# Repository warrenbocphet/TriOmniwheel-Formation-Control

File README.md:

# 3-OmniWheels-Rover-Platform
This project developed by students in [the University of Adelaide](https://ecms.adelaide.edu.au/electrical-electronic-engineering/) during the Summer Research project 2018-2019, which developed a 3WD  rover platform for autonomous multi-agent systems.

## Overview:
>The distributed system will contain multiple agents. Each agent can make its own decision. However, the four agents still need to communicate with each other about the velocity, the current position, the destination and the angle of the agent. This allows an agreement to be made to achieve the desired formation.

## Hardware setup:
Motor: 251RPM DC geared (43.7:1) motor w/ ecoder.

Encoder: 64 resolution => 2797 count per rotation.

Control board: Arduino Due for controlling, Arduino MKR1000 for WiFi communication.

## Example
### Simple case (user generated coordinate/path)
Real data feedback and put into simulation

Real demo. Noticed how the position of the rovers and the feedback position is not entirely the same. Overtime, the system introduce more and more error. Since the system is self guidance, there's no correction during performance.

### Formation control without collision avoidance
Generate path to form a triangle formation. Connected circle represent rover with radius, dash circle represent the safety distance (collision avoicedance is not implement in the GIF below).

The same triangle formation with different starting position. Noticed how the formation is rotated with these starting positions. The algorithm [1] does not try to get to a specific coordinate but rather a formation (i.e, a triangle, circle or any arbitrary topology).

### Formation control with collision avoidance
The collision avoidance will be explained further down, let's first have a look at the simulation and the result:

#### Hexagon

#### Triangle

#### X shape

#### Cross

#### Accumulating error (youtube link)

#### Reducing accumulating error by reducing the speed (youtube link)

## Reference
[1] Fathian, Kaveh & Safaoui, Sleiman & Summers, Tyler & Gans, Nicholas. (2018). Robust Distributed Planar Formation Control for Higher-Order Holonomic and Nonholonomic Agents. Link: https://www.researchgate.net/publication/326696917_Robust_Distributed_Planar_Formation_Control_for_Higher-Order_Holonomic_and_Nonholonomic_Agents

The author's website: https://sites.google.com/view/kavehfathian/home?authuser=0

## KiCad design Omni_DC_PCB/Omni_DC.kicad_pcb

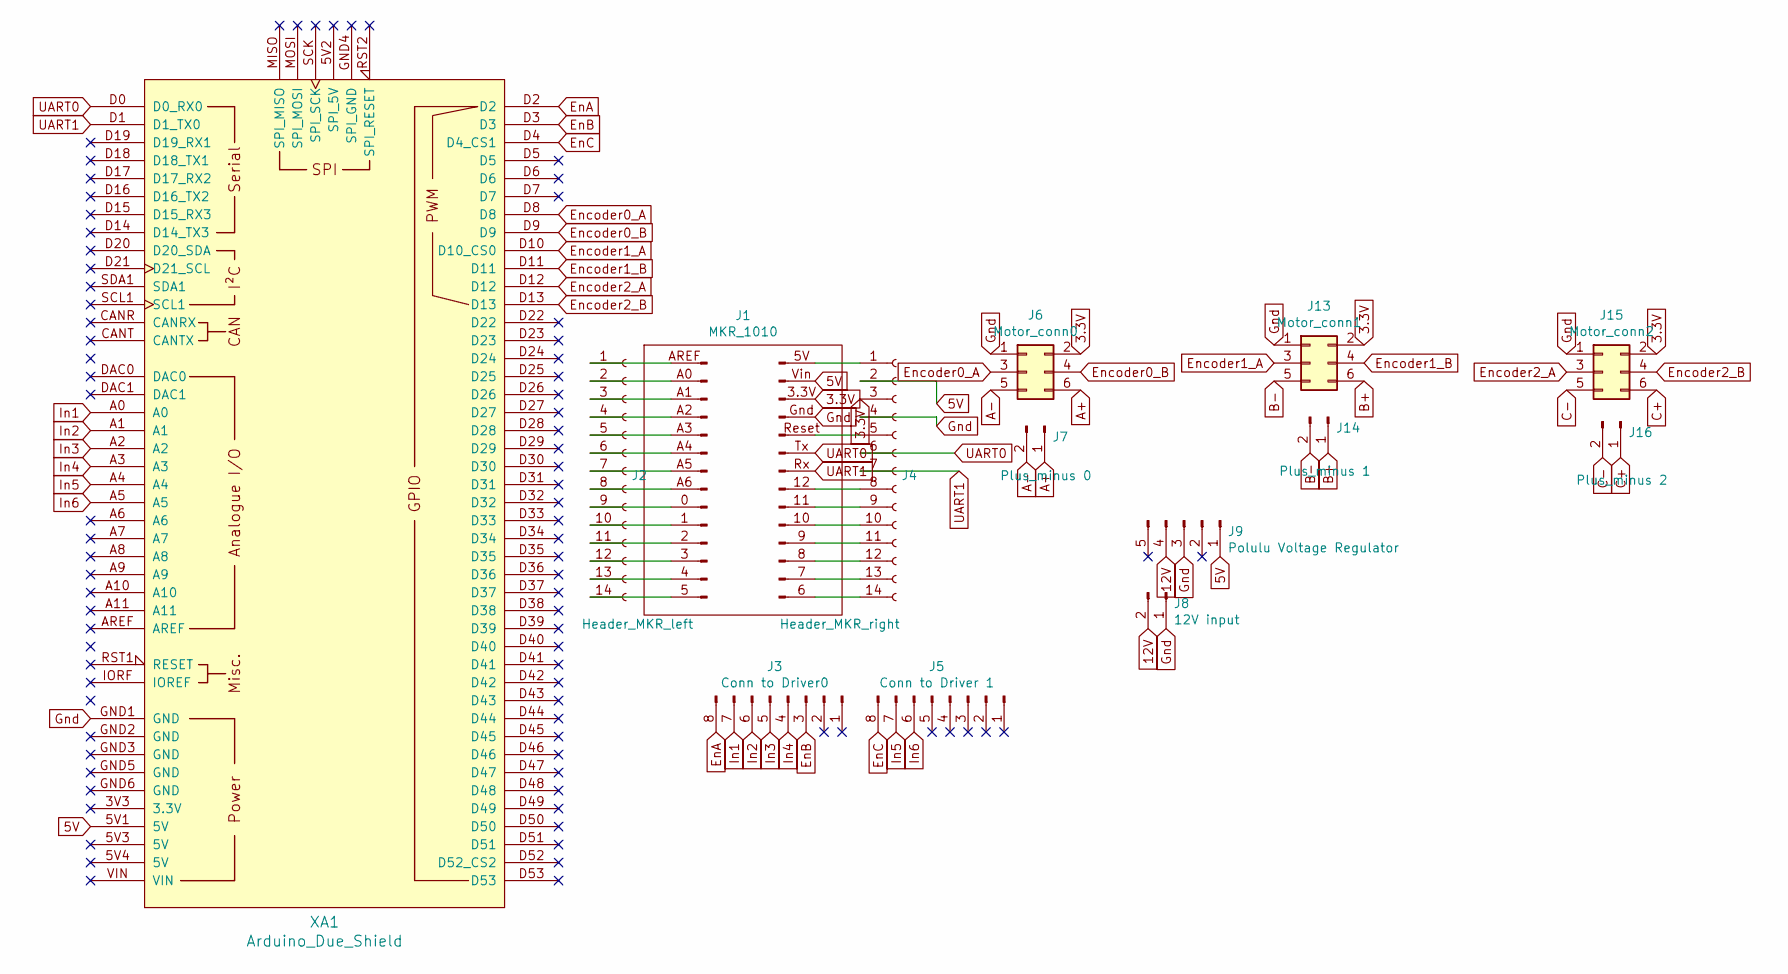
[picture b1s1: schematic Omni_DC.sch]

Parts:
J1: MKR_1010
J2: Header_MKR_left; PinHeader_1x14_P2.54mm_Vertical
J3: Conn to Driver0; PinHeader_1x08_P2.54mm_Vertical
J4: Header_MKR_right; PinHeader_1x14_P2.54mm_Vertical
J5: Conn to Driver 1; PinHeader_1x08_P2.54mm_Vertical
J6: Motor_conn0; PinHeader_2x03_P2.54mm_Vertical
J7: Plus_minus 0; PinHeader_1x02_P2.54mm_Vertical
J8: 12V input; PinHeader_1x02_P2.54mm_Vertical
J9: Polulu Voltage Regulator; PinHeader_1x05_P2.54mm_Vertical
J13: Motor_conn1; PinHeader_2x03_P2.54mm_Vertical
J14: Plus_minus 1; PinHeader_1x02_P2.54mm_Vertical
J15: Motor_conn2; PinHeader_2x03_P2.54mm_Vertical
J16: Plus_minus 2; PinHeader_1x02_P2.54mm_Vertical
XA1: Arduino_Due_Shield

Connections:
3.3V: J1.3.3V (Pin_3), J4.3, J6.2, J13.2, J15.2
5V: J1.Vin (Pin_2), J4.2, J9.1, XA1.5V1 (5V)
12V: J8.2, J9.4
A+: J6.6, J7.1
A-: J6.5, J7.2
B+: J13.6, J14.1
B-: J13.5, J14.2
C+: J15.6, J16.1
C-: J15.5, J16.2
EnA: J3.8, XA1.D2
EnB: J3.3, XA1.D3
EnC: J5.8, XA1.D4 (D4_CS1)
Encoder0_A: J6.3, XA1.D8
Encoder0_B: J6.4, XA1.D9
Encoder1_A: J13.3, XA1.D10 (D10_CS0)
Encoder1_B: J13.4, XA1.D11
Encoder2_A: J15.3, XA1.D12
Encoder2_B: J15.4, XA1.D13
Gnd: J1.Gnd (Pin_4), J4.4, J6.1, J8.1, J9.3, J13.1, J15.1, XA1.GND1 (GND)
In1: J3.7, XA1.A0
In2: J3.6, XA1.A1
In3: J3.5, XA1.A2
In4: J3.4, XA1.A3
In5: J5.7, XA1.A4
In6: J5.6, XA1.A5
unnamed: J1.0 (Pin_6), J2.9
unnamed: J1.1 (Pin_5), J2.10
unnamed: J1.2 (Pin_4), J2.11
unnamed: J1.3, J2.12
unnamed: J1.4 (Pin_2), J2.13
unnamed: J1.5 (Pin_1), J2.14
unnamed: J1.5V (1), J4.1
unnamed: J1.6 (Pin_14), J4.14
unnamed: J1.7 (Pin_13), J4.13
unnamed: J1.8 (Pin_12), J4.12
unnamed: J1.9 (Pin_11), J4.11
unnamed: J1.10, J4.10
unnamed: J1.11 (Pin_9), J4.9
unnamed: J1.12 (Pin_8), J4.8
unnamed: J1.A0 (Pin_13), J2.2
unnamed: J1.A1 (Pin_12), J2.3
unnamed: J1.A2 (Pin_11), J2.4
unnamed: J1.A3 (Pin_10), J2.5
unnamed: J1.A4 (Pin_9), J2.6
unnamed: J1.A5 (Pin_8), J2.7
unnamed: J1.A6 (Pin_7), J2.8
unnamed: J1.AREF (Pin_14), J2.1
unnamed: J1.Reset (Pin_5), J4.5
UART0: J1.Tx (Pin_6), J4.6, XA1.D0 (D0_RX0)
UART1: J1.Rx (Pin_7), J4.7, XA1.D1 (D1_TX0)

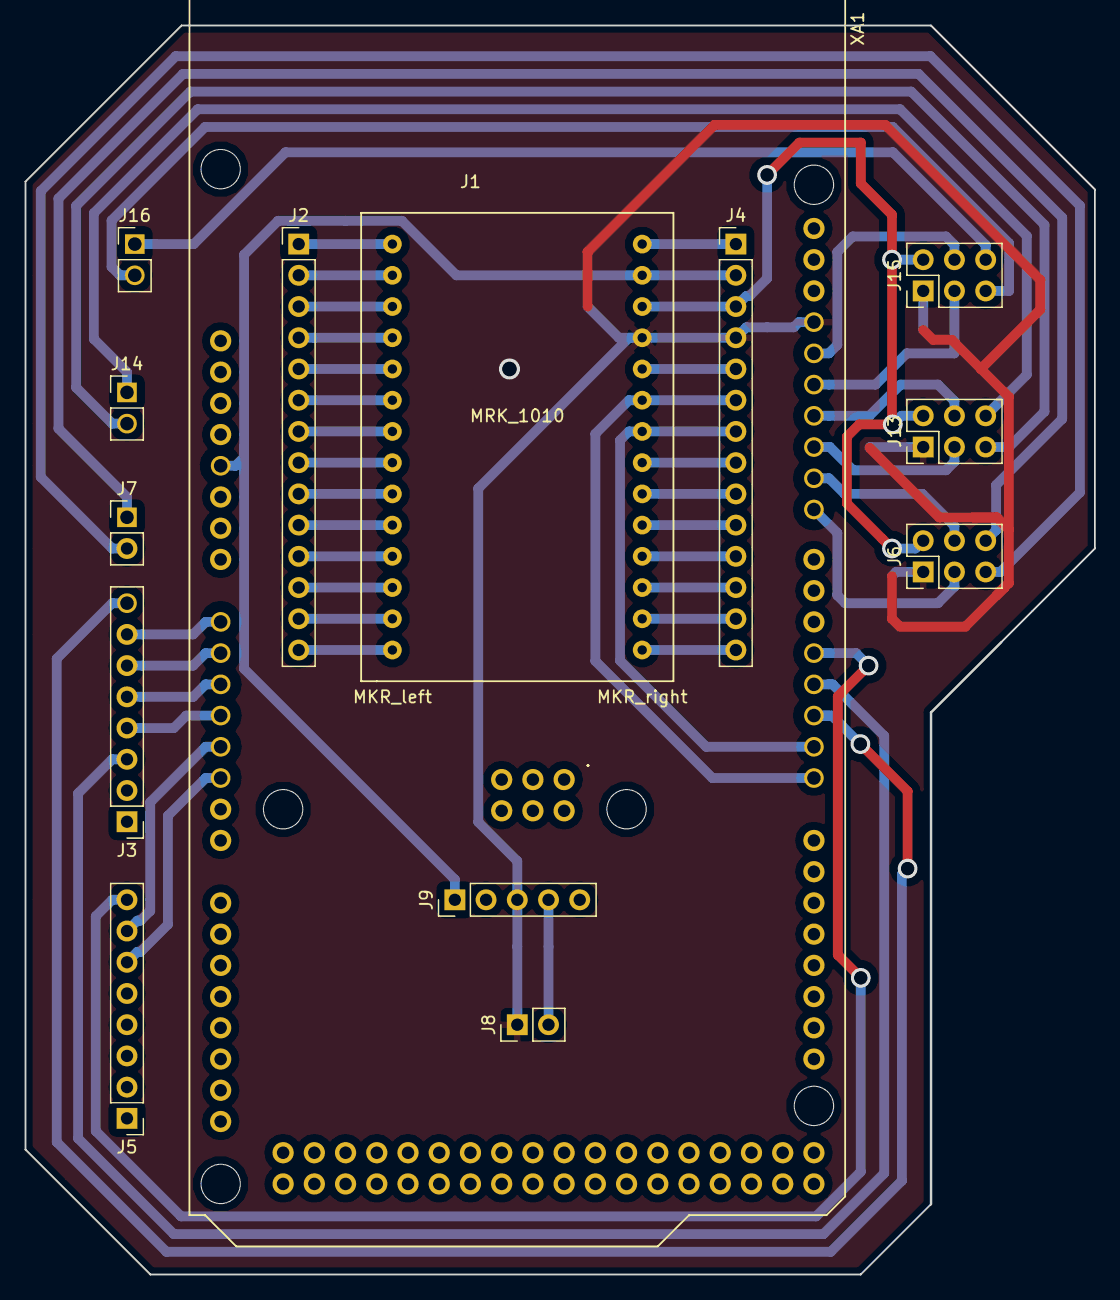
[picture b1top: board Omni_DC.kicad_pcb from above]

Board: 2 copper layers, 87.0 x 101.6 mm, 14 parts (0 on the bottom side), 50 nets.

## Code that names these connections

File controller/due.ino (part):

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///////////////////////////// DC motors /////////////////////////////
const int int1 = A0; // motor 0
const int int2 = A1;
const int enA = 2;
int pwm0;

const int int3 = A2; // motor 1
const int int4 = A3;
const int enB = 3;
int pwm1;

const int int5 = A4; // motor 2
const int int6 = A5;
const int enC = 4;
int pwm2;

float rover_radius = 13.7; // in cm
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
  pinMode(int1, OUTPUT);
  pinMode(int2, OUTPUT);
  pinMode(enA, OUTPUT);

  pinMode(int3, OUTPUT);
  pinMode(int4, OUTPUT);
  pinMode(enB, OUTPUT);

  pinMode(int5, OUTPUT);
  pinMode(int6, OUTPUT);
  pinMode(enC, OUTPUT);

  analogWrite(enA, 0);
  analogWrite(enB, 0);
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
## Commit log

2018-12-30 Add files via upload
    Arduino sketch that controls the speed of each wheel.
2018-12-30 Add files via upload
    The algorithm used to calculate the required speed of each wheel to reach the position and when to run those speed.
2018-12-30 Add files via upload
    API for the controller. Use to send and receive data through serial communication (UART) between Raspberry Pi and Arduino.
2018-12-30 Rename rapi0.py to rapi.py
2018-12-30 Update roverScheduler.py
    Fixed below bugs:
    - Cannot go to negative y
    - Cannot rotate on the spot
    - Cannot rotate to counterclockwise
2018-12-30 Update roverScheduler.py
    Create an upper limitation on how big the angular velocity can be.
2019-01-04 Update roverScheduler.py
    Fix a bug where rover can't run to negative x coordinate.
2019-01-07 Update roverScheduler.py
    Fix a bug where rover can't go to the same destination as the current destination.
2019-01-07 Update roverScheduler.py
    Fix a bug where rover would try to rotate even when the difference is ~0.
2019-01-07 Update roverScheduler.py
    fix a small bug
2019-01-08 Update and rename simpleRover.ino to controllerArduino.ino
    Move all the controller part from RPI to Arduino.
2019-01-09 Update controllerArduino.ino
    Fix some minor bugs and add an ability to reset the current state of the rover back to [0, 0, 0].
2019-01-09 Delete roverScheduler.py
    A scheduler is not necessary anymore.
2019-01-10 Update controllerArduino.ino
    Fix some major bugs:
    - Rover won't turn in ACC direction if the speed required to turn exceeds the threshold speed.
    - Sometimes can't meet the stopping condition.
    - After recalculating v0s, v1s, v2s, I forgot to recalculate v0, v1, and v2.
    And some minor bugs.
2019-01-10 Add files via upload
    Add testbench1 (non blocking when go to the destination, in other words, destination can be changed mid way)
    Add manual control which allows the user to put whatever he/she wants it to go.
2019-01-10 Update controllerArduino.ino
    Update to support both testbench1 and testbench2
2019-01-10 Rename testbench1.py to testbench/testbench1.py
2019-01-10 Add files via upload
    Same as testbench1 but now blocking instead of nonblocking.
2019-01-10 Update rapi.py
    Support RPI GUI
2019-01-10 Update controllerArduino.ino
    Support RPI GUI
2019-01-10 Add a function as requested by Vernon.
    The rover takes 1 more input (time) and rover only going to that point if the timer goes pass the input time.
2019-01-10 Update rapi.py
    Send an extra input (time).
2019-01-10 Rename manualControl.py to testbench/manualControl.py
2019-01-21 Update controllerArduino.ino
    Add IMU sensor
2019-01-22 Update controllerArduino.ino
    Added HPF to Gyro readings, LPF to Accel readings and complimentary filter for both afterwards.
2019-01-22 Update controllerArduino.ino
    Change how I calibrate the sensor
2019-01-27 Add files via upload
    Use to test how well the sensor feedback doing.
2019-01-27 Rename test_feedback_speed.ino to test/test_feedback_speed.ino
2019-01-27 Rename getData.py to test/getData.py
2019-01-28 Update test_feedback_speed.ino
    Test 3 wheels at the same time.
2019-01-29 Update test_feedback_speed.ino
    can change time frame more easily
2019-01-29 Add files via upload
    Run through Kalman Filter and then plot the data.
2019-01-29 Update test_feedback_speed.ino
    Remove complimentary filter.
2019-01-30 Update controllerArduino.ino
    Add Kalman Filtering.
2019-01-31 Update controllerArduino.ino
    Use IMU sensors feedback.
2019-01-31 Update controllerArduino.ino
    Bug fixed.
2019-01-31 Update controllerArduino.ino
    Bug fixes. (rover not able to keep track of Oxy)
2019-02-01 Update controllerArduino.ino
    More bugs fixed.
    Add the ability to control the constant speed.
2019-02-02 Add files via upload
    Add on board GUI.
2019-02-02 Rename GUIwithHost.py to GUI/GUIwithHost.py
2019-02-02 Rename GUI.py to GUI without Host/GUI.py
2019-02-02 Rename GUI without Host/GUI.py to GUI/GUI_without_host.py
2019-02-02 Rename GUIwithHost.py to GUI_with_Host.py
2019-02-02 Rename controllerArduino.ino to controller/controllerArduino.ino
2019-02-02 Rename rapi.py to controller/rapi.py
2019-02-02 Rename test/getData.py to testbench/test/getData.py
2019-02-02 Rename test/plotData.py to testbench/test sensor data/plotData.py
2019-02-02 Rename test/test_feedback_speed.ino to testbench/test sensor data/test_feedback_speed.ino
2019-02-02 Rename testbench/test/getData.py to testbench/test sensor data/getData.py
2019-02-04 Add files via upload
    Laser cutting file for the platform
2019-02-04 Rename testbench/manualControl.py to testbench/test movement/manualControl.py
2019-02-04 Rename testbench/testbench1.py to testbench/test movement/testbench1.py
2019-02-04 Rename testbench/testbench2.py to testbench/test movement/testbench2.py
2019-03-24 Update controllerArduino.ino
    Update communication protocol.
2019-03-24 Update and rename hostComp_controller.py to textGUI.py
    Update communication protocol.
2019-03-26 Rename server.py to Barebone communication/server.py
2019-03-28 Update and rename controllerArduino.ino to due.ino
    Switch to a system with 2 different Arduino. This one is for the Due which directly control the motors.
2019-03-28 Rename mkr1010_v0.2.ino to mkr1010.ino
2019-03-28 Update textGUI.py
    Improve socket communication.
2019-04-09 Update due.ino
    Change the rover radius.
2019-04-09 Update mkr1010.ino
    Added LCD display.
2019-04-09 Update due.ino
    Increase the speed toward the end.
2019-04-11 Update due.ino
    change PID parameter
2019-04-11 Update due.ino
    1. Fix a bug where "phi" data keep resetting back to 0 (because of typecasting)
    2. Increase accuracy by taking in account of slippage.
2019-04-11 Update and rename mkr1010.ino to mkr1000.ino
    Switch back to MKR1000 to save money.
2019-04-13 Update due.ino
    Give the ability to change the current coordinate (the rover won't move since the target is then equal to current coordinate).
2019-04-13 Update mkr1000.ino
    Add new thing to support new update to the Due.
2019-04-14 Update due.ino
    Add option to just set current coordinate to something else, rather than set both coordinate and target to something else.
2019-04-14 Update mkr1000.ino
    Add option to send back ID.
2019-04-14 Update and rename textGUI.py to server.py
    Add more option to the text GUI.
2019-04-15 Update formation_control.py
    Add OOP element.
2019-04-18 Update formation_control.py
    Fix a bug.
2019-05-14 Update formation_control.py
    All rover will move after all reach the destination of 1 iteration.
2019-05-16 Update due.ino
    Fix a bug where it would flip the Y axis.
2019-05-16 Update mkr1000.ino
    Fix a bug where it would flip the Y axis.
2019-05-16 Update formation_control.py
    Maintaining the code base
2019-05-22 Add files via upload
    Added path generator
2019-05-22 Rename distributed_formation_control2.py to path_generator.py
2019-05-23 Update path_generator.py
    I don't know if there's any change on this but just to be sure before I add some more features.
2019-05-23 Update simulation.py
    Make simulation to be callable by path_generator.
2019-05-23 Update path_generator.py
    Add scaling factor to desired formation.
2019-05-23 Add files via upload
    In a perfect world, I would test before commit but I got tired and just commit this to backup. There's no way this would work so don't even try.
2019-05-25 Update formation_control.py
    Add some more formation. Next commit will be collision avoidance.
2019-05-25 Update path_generator.py
    Add collision avoidance.
    Add T formation.
2019-05-25 Update and rename collision_avoicedance.py to collision_avoidance.py
    It seems like collision avoidance is working somewhat ok now.
    However, I keep come across 2 problems:
    1. Deadlock (which is kinda expected)
    2. Rover crash before the algorithm even start
    I will look into this more later on.
2019-05-26 Update collision_avoidance.py
    Fix a bug causing the rover to not move when it need to move vice versa. (change the condition when rover stop moving)
2019-05-26 Update path_generator.py
    Add control vector output.
2019-05-26 Update simulation.py
    Add control vector plotting.
2019-05-26 Update simulation.py
    Fix a bug where when you run path_generator.py, it would simulate the previous path, not the current one.
2019-06-07 Update and rename formation_control.py to control_interface.py
    Change the interface such that the script would keep loading in new formations until we told it to stop.
2019-06-08 Update control_interface.py
    Erase past formation every time load in new one.
2019-06-12 Update control_interface.py
    Add the ability to read the first line as the initial position.
2019-07-25 Update path_generator.py
    I change matrix to array since matrix suck.
2019-07-25 Update collision_avoidance.py
    I change matrix to array.
2019-07-25 Update control_interface.py
    I combine path_generator to the control interface because back then, the control interface has to read from a text file, which is not dynamic. However, you can't foresee the path anymore.
2019-07-25 Update collision_avoidance.py
    I changed the way to calculate the angle between 2 vectors, from using dot product to cross product.
    I also improve the algorithm to choose the angle to turn.
